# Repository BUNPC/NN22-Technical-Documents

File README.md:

This repository contains the technical documentation used to create all parts of the NN22 whole-head fNIRS system.

A description of the documents contained in this respository and other instructions related to the ninjaNIRS system can be found at openfnirs.org [here](https://openfnirs.org/hardware/ninjanirs2022/).

Please use the [Hardware Forum](https://openfnirs.org/community/hardware-forum/) at openfnirs.org to discuss anything about the ninjaNIRS system.

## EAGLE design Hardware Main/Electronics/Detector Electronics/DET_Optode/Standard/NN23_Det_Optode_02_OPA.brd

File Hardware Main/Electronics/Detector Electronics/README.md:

# Detector Electronics
## Updated 5 August, 2024

All detector related files are located within this folder.

Two versions of the backplane are available, the 6 layer and single layer. The 6 layer folder contains the files for the full height backplane to allow for up to 6 detector interface cards to be connected and the single layer folder contains the files for the system configuration with only one interface card per backboard slot.

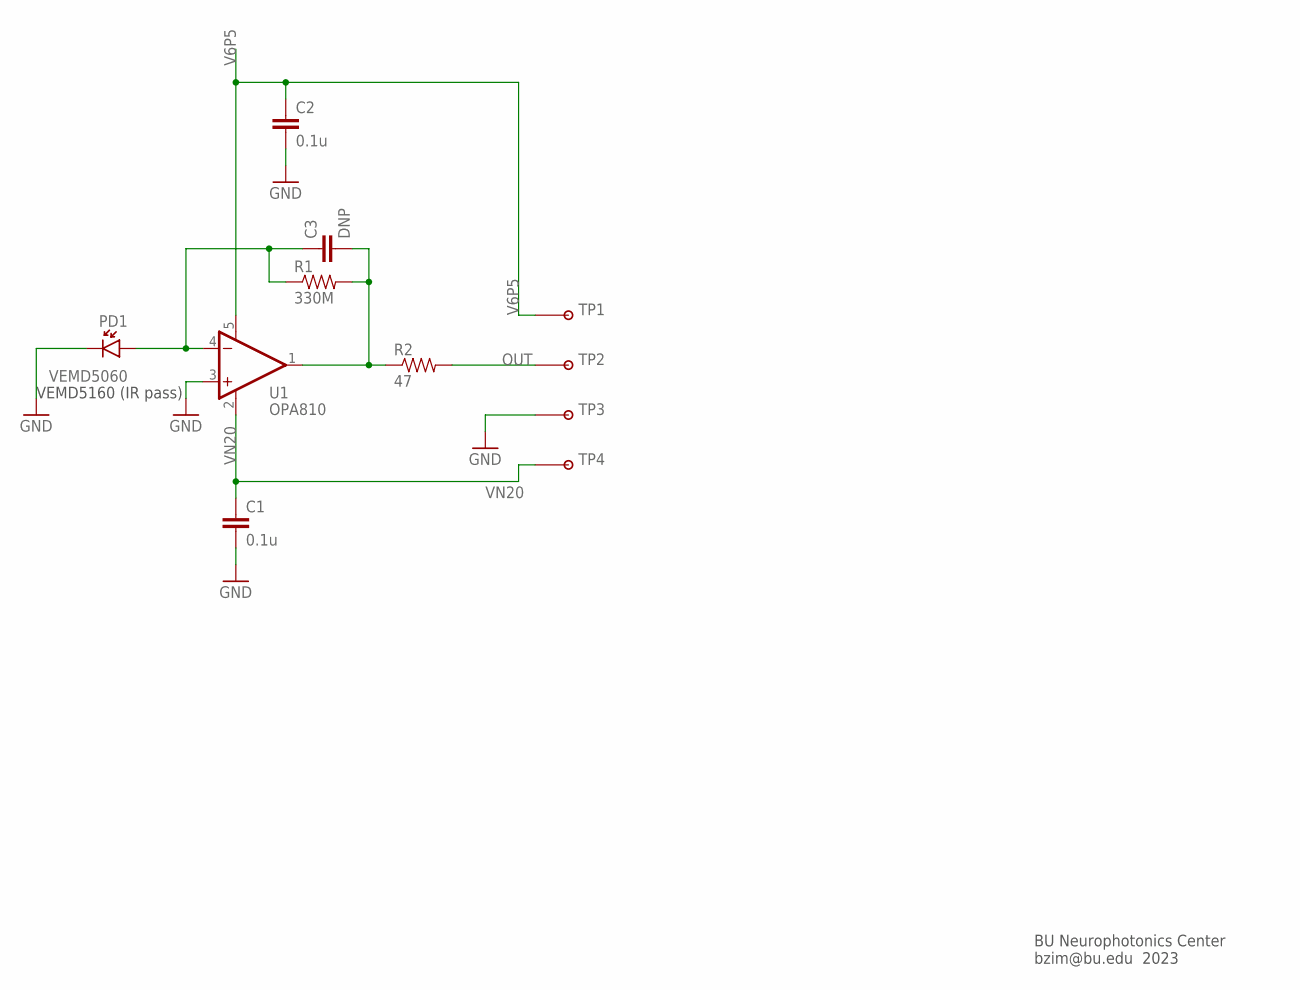
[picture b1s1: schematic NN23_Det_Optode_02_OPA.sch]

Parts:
C1, C2: 0.1u; 0402-CAP
C3: DNP; 0402-CAP
PD1: VEMD5060
R1: 330M; 0402-RES
R2: 47; 0402-RES
TP1, TP2, TP3, TP4: TESTPOINTPADSMALL; TESTPAD_SMALL
U1: OPA810; SOT353

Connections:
GND: C1.2, C2.2, PD1.C1 (C), PD1.C2 (C), TP3.P$1, U1.3 (+IN)
unnamed: C3.2, R1.2, R2.1, U1.1 (OUT)
unnamed: C3.1, PD1.A, R1.1, U1.4 (-IN)
OUT: R2.2, TP2.P$1
V6P5: C2.1, TP1.P$1, U1.5 (V+)
VN20: C1.1, TP4.P$1, U1.2 (V-)

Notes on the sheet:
VEMD5160 (IR pass)
BU Neurophotonics Center bzim@bu.edu 2023

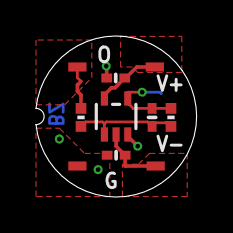
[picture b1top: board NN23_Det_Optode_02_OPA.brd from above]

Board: 2 copper layers, 8.9 x 8.9 mm, 11 parts (1 on the bottom side), 6 nets.

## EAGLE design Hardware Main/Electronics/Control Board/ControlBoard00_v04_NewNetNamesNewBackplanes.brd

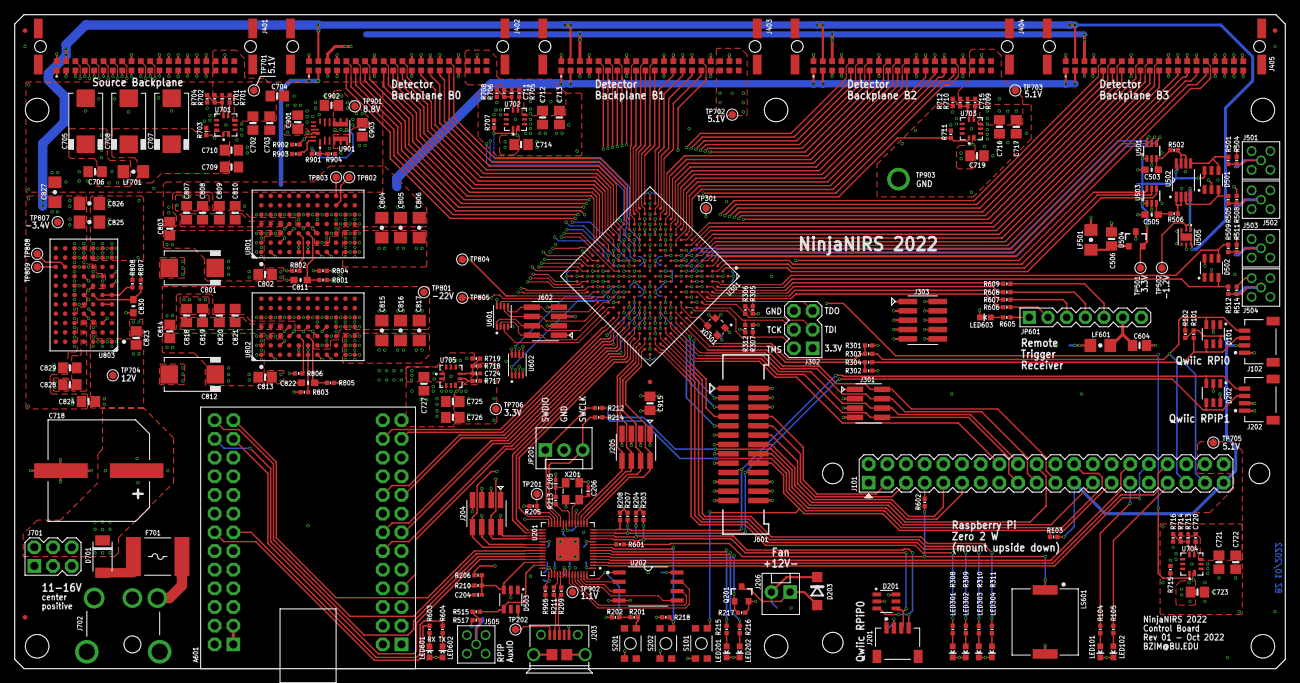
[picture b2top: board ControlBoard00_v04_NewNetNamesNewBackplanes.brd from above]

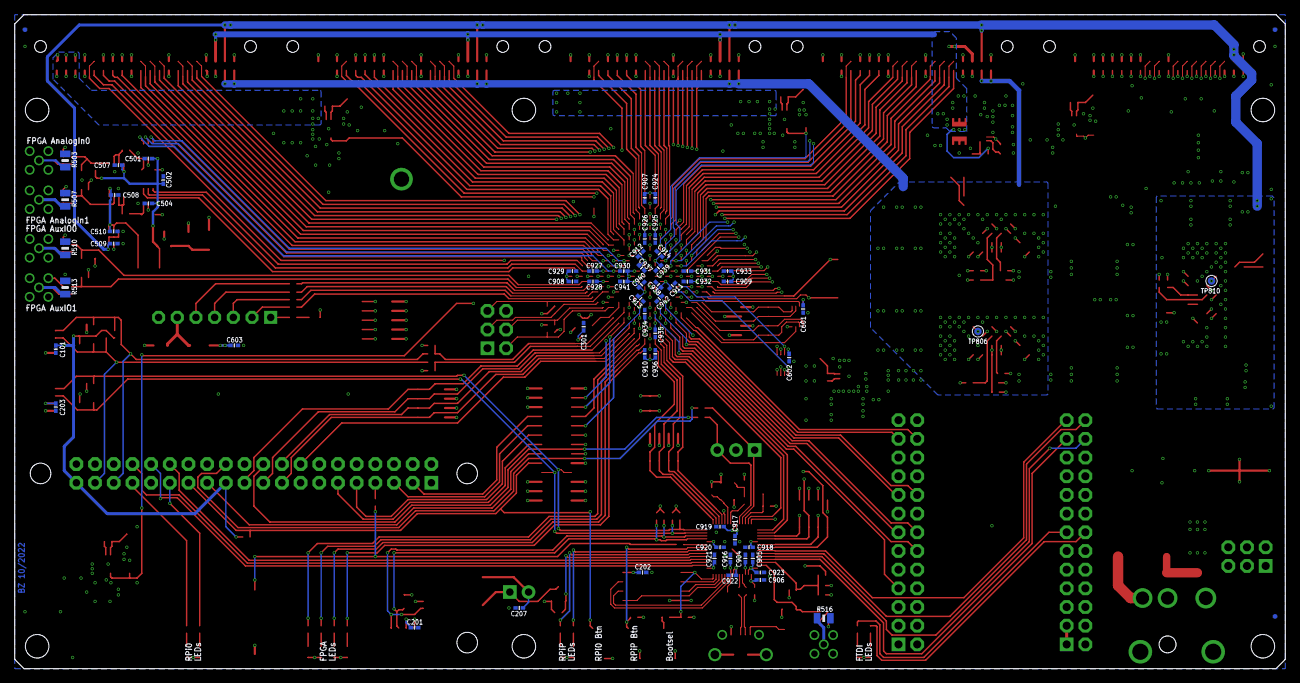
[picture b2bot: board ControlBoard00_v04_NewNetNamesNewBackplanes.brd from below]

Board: 6 copper layers, 172.7 x 88.9 mm, 323 parts (64 on the bottom side), 316 nets.

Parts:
A601: FT2232H-MINIMOD
C101, C201, C202, C203, C204, C207, C301, C501, C504, C507, C508, C601, C602, C603, C916, C917, C918, C919, C920, C921, C922, C923, C924, C925, C926, C927, C928, C929, C930, C931, C932, C933, C934, C935, C936, C937, C938, C939, C940, C941, C942: 0.1u; 0402-CAP
C205, C206: 27p; 0402-CAP
C502, C509, C510, C904, C905, C906, C907, C908, C909, C910, C911, C912, C913, C914: 4.7u; 0402-CAP
C503, C505: 18n; 0603-CAP
C506, C604, C702, C703, C704, C706, C709, C710, C712, C713, C714, C716, C717, C719, C721, C722, C723, C725, C726, C727, C901, C902, C903: 22u; 0805-CAP
C701, C711, C715, C720, C724: 39p; 0402-CAP
C705, C707, C708, C801, C812: 100u/25V; 2917-CAP
C718: 470u/25V; CAP-SMD-POL-12.5
C802, C803, C807, C808, C809, C810, C813, C814, C818, C819, C820, C821, C823, C824, C828, C829: 4.7u; 0805-CAP
C804, C805, C806, C815, C816, C817: 10u; 1206
C811, C822, C830: 1u; 0603-CAP
C825, C826: 100u; 1206
C827: DNP; 1206
C915: DNP; 0805-CAP
D101, D201, D202, D501, D502, D503: D1213A-02SO; SOT23-6
D203: SOD123
D701: SOD128
F701: 2920L600/16MR; 2920-FUSE
FID901, FID902, FID903, FID904, FID905, FID906, FID907: FIDUCIALUFIDUCIAL; MICRO-FIDUCIAL
J101: M20X2_PTH
J102, J201, J202: M04X1_JST_SH_RA; M04X1_JST_SH_SM_RA
J203: USB-MICRO
J204, J205, J301, J602: M04X2_0.050_SMD_NO_CREAM
J206: M02POLAR; MOLEX-1X2
J302, J701: M03X2PTH; 2X3-NS
J303: M05X2_SMD_0.050_NOCREAM; M05X2_0.050_SMD_NO_CREAM
J401, J402, J403, J404, J405: M20X2_HARFLEX_M
J501, J502, J503, J504, J505: SMAMMCX_PTH; MMCX_PTH_STR
J601: M13X2_0.050_SHF
J702: POWERJACK_PJ051AH; PJ051AH
JP201: MOLEX-1X3
JP601: TLW-107-05-G-S; 1X07
LED101, LED201, LED301, LED303, LED601: LTST-C191KRKT; LED-0603
LED102, LED202, LED302, LED304, LED602, LED603: LTST-C191KGKT; LED-0603
LF501, LF601, LF701: FERRITE1206; 1206
LS601: PKMCS0909E4000-R1; XDCR_PKMCS0909E4000-R1
Q201: MOSFET-NCHANNELSMD; SOT23-3
R101, R102, R103, R203, R204, R207, R208, R210, R218, R301, R302, R305, R306, R307, R312, R504, R508, R511, R514, R517: 10k; 0402-RES
R104, R105, R215, R216, R308, R309, R310, R311, R603, R604, R605: 470; 0402-RES
R201, R213, R501, R505, R601, R602, R606, R607, R608, R609, R701, R705, R709, R713, R717: 1k; 0402-RES
R202, R212, R214, R303, R304, R903: DNP; 0402-RES
R205, R217, R703, R707, R711, R715, R804, R902: 100k; 0402-RES
R206, R702, R706, R710, R714, R718: 47k; 0402-RES
R209, R211, R502, R506: 27; 0402-RES
R503, R507, R510, R513, R516: DNP; 0805
R509, R512, R515, R905: 100; 0402-RES
R704, R708, R712, R716: 8.66k; 0402-RES
R719: 15k; 0402-RES
R801, R805: 82; 0402-RES
R802, R806: 180k; 0402-RES
R803: 220k; 0402-RES
R807: 15; 0402-RES
R808, R901: 68k; 0402-RES
R904: 6.8k; 0402-RES
S101, S201, S202: SWITCH-MOMENTARY-2SMD-3; TACTILE_SWITCH_SMD-3
TP201, TP202, TP301, TP501, TP502, TP701, TP702, TP703, TP704, TP705, TP706, TP801, TP802, TP803, TP804, TP805, TP806, TP807, TP808, TP809, TP810, TP901, TP902: TESTPOINT_ROUND; TESTPAD_ROUND
TP903: TESTPOINTTUR; TURRET
U201: RP2040; QFN-56_EP
U202: W25Q_SO; SO08-208MIL
U301: MACHXO2_FTBGA256; LBGA-256
U501, U503: ADS7886; SOT363
U502: LT1801; SOP65P490X110-8N
U504: REF30XX; SOT23-3
U505: ADP7182_WSON; WSON6
U601, U602: APS6404L; USON8L-2X3MM
U701, U702, U703, U704, U705: RPL-30
U801, U802, U803: LTM4651; BGA-77
U901: MPM3620_FULL_CREAM; QFN-20-MPS_FULL_CREAM
X201: CRYSTAL-3.2-2.5
XO301: OSCILLATOR_TXO2520; TXO2520

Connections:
ADS_CSN0: U301.H5, U501.6
ADS_CSN1: U301.C1, U503.6
ADS_SCK0: U301.F5, U501.4
ADS_SCK1: U301.B1, U503.4
ADS_SDO0: U301.G5, U501.5
ADS_SDO1: U301.C2, U503.5
AUXIO0: D502.4, R509.2, U301.B3
AUXIO1: D502.3, R512.2, U301.A3
BOOTSEL: R201.1, S201.4
DETB_END_CYC0: J402.B15, U301.R7
DETB_END_CYC1: J403.B15, U301.P1
DETB_END_CYC2: J404.B15, U301.J1
DETB_END_CYC3: J405.B15, U301.D1
DETB_RUN0: J402.A16, U301.T5
DETB_RUN1: J403.A16, U301.N3
DETB_RUN2: J404.A16, U301.K5
DETB_RUN3: J405.A16, U301.E3
DETB_SELECT00: J402.B11, U301.R9
DETB_SELECT01: J402.B9, U301.R11
DETB_SELECT02: J402.A10, U301.T9
DETB_SELECT03: J402.B7, U301.N9
DETB_SELECT04: J402.B5, U301.N11
DETB_SELECT05: J402.A6, U301.P9
DETB_SELECT06: J403.B11, U301.T2
DETB_SELECT07: J403.B9, U301.T4
DETB_SELECT08: J403.A10, U301.R4
DETB_SELECT09: J403.B7, U301.P5
DETB_SELECT10: J403.B5, U301.N8
DETB_SELECT11: J403.A6, U301.N6
DETB_SELECT12: J404.B11, U301.K2
DETB_SELECT13: J404.B9, U301.M2
DETB_SELECT14: J404.A10, U301.M1
DETB_SELECT15: J404.B7, U301.J4
DETB_SELECT16: J404.B5, U301.L4
DETB_SELECT17: J404.A6, U301.L3
DETB_SELECT18: J405.B11, U301.F2
DETB_SELECT19: J405.B9, U301.H2
DETB_SELECT20: J405.A10, U301.G1
DETB_SELECT21: J405.B7, U301.F4
DETB_SELECT22: J405.B5, U301.H4
DETB_SELECT23: J405.A6, U301.G3
DETB_STATUS_SELECT0: J402.B16, U301.R6
DETB_STATUS_SELECT1: J403.B16, U301.N2
DETB_STATUS_SELECT2: J404.B16, U301.J2
DETB_STATUS_SELECT3: J405.B16, U301.D2
DETB_TRIGGER0: J402.B14, U301.T7
DETB_TRIGGER1: J403.B14, U301.P2
DETB_TRIGGER2: J404.B14, U301.J3
DETB_TRIGGER3: J405.B14, U301.E2
EXP_J303_D0: J303.2, U301.C5
EXP_J303_D1: J303.4, U301.D6
EXP_J303_D2: J303.6, U301.D7
EXP_J303_D3: J303.8, U301.C7
EXP_J601_D0: J601.3, U301.C10
EXP_J601_D1: J601.5, U301.B10
EXP_J601_D2: J601.7, U301.A13
EXP_J601_D3: J601.9, U301.E10
EXP_J601_D4: J601.11, U301.D11
EXP_J601_D5: J601.13, U301.C12
EXP_J601_D6: J601.15, U301.C13
FP_LED0: R308.2, U301.A15
FP_LED1: R309.2, U301.B14
FP_LED2: R310.2, U301.A14
FP_LED3: R311.2, U301.B13
FP_SCL: R301.1, R303.1, U301.A9
FP_SDA: R302.1, R304.1, U301.C9
FT_C0: A601.CN2-18, U301.G16
FT_C1: A601.CN2-17, U301.G15
FT_C2: A601.CN2-20, U301.H13
FT_C5: A601.CN2-24, U301.H16
FT_C6: A601.CN2-23, U301.H15
FT_CTS#: A601.CN3-23, U201.39
FT_D4: A601.CN2-14, U301.G12
FT_D5: A601.CN2-13, U301.F16
FT_D6: A601.CN2-16, U301.G14
FT_D7: A601.CN2-15, U301.G13
FT_RTS#: A601.CN3-24, U201.38
FT_RXD: A601.CN3-25, U201.36
FT_TXD: A601.CN3-26, U201.37
GND: A601.CN2-2, A601.CN2-4, A601.CN2-6, A601.CN3-2, A601.CN3-4, C101.2, C201.2, C202.2, C203.2, C204.2, C205.2, C206.2, C207.2, C301.2, C501.2, C502.2, C503.2, C504.2, C505.2, C506.2, C507.2, C508.1, C509.1, C510.1, C601.2, C602.2, C603.2, C604.2, C702.2, C703.2, C704.2, C705.N, C706.2, C707.N, C708.N, C709.2, C710.2, C712.2, C713.2, C714.2, C716.2, C717.2, C718.N, C719.2, C721.2, C722.2, C723.2, C725.2, C726.2, C727.2, C801.N, C802.2, C804.1, C805.1, C806.1, C807.2, C808.2, C812.N, C813.2, C815.1, C816.1, C817.1, C818.2, C819.2, C823.2, C825.1, C826.1, C827.1, C828.2, C901.2, C902.2, C903.2, C904.2, C905.2, C906.2, C907.2, C908.2, C909.2, C910.2, C911.2, C912.2, C913.2, C914.2, C915.2, C916.2, C917.2, C918.2, C919.2, C920.2, C921.2, C922.2, C923.2, C924.2, C925.2, C926.2, C927.2, C928.2, C929.2, C930.2, C931.2, C932.2, C933.2, C934.2, C935.2, C936.2, C937.2, C938.2, C939.2, C940.2, C941.2, C942.2, D101.2, D201.2, D202.2, D501.2, D502.2, D503.2, J101.1, J101.8, J101.12, J101.15, J101.22, J101.28, J101.31, J101.36, J102.1, J201.1, J202.1, J203.5, J203.SH1, J203.SH2, J203.SH3, J203.SH4, J203.SH5, J203.SH6, J204.1, J204.3, J204.5, J204.7, J205.1, J205.3, J205.5, J205.7, J301.1, J301.3, J301.5, J301.7, J302.6, J303.1, J303.3, J303.5, J303.7, J303.9, J401.A1, J401.A9, J401.A12, J401.A13, J401.A14, J401.A15, J401.A16, J401.A17, J401.A19, J401.B1, J401.B2, J401.B3, J401.B17, J402.A1, J402.A4, J402.A8, J402.A12, J402.A13, J402.A14, J402.A15, J402.A17, J402.A19, J402.B3, J402.B4, J402.B8, J402.B12, J402.B17, J403.A1, J403.A4, J403.A8, J403.A12, J403.A13, J403.A14, J403.A15, J403.A17, J403.A19, J403.B3, J403.B4, J403.B8, J403.B12, J403.B17, J404.A1, J404.A4, J404.A8, J404.A12, J404.A13, J404.A14, J404.A15, J404.A17, J404.A19, J404.B3, J404.B4, J404.B8, J404.B12, J404.B17, J405.A1, J405.A4, J405.A8, J405.A12, J405.A13, J405.A14, J405.A15, J405.A17, J405.A19, J405.B3, J405.B4, J405.B8, J405.B12, J405.B17, J501.G@1, J501.G@2, J501.G@3, J501.G@4, J502.G@1, J502.G@2, J502.G@3, J502.G@4, J503.G@1, J503.G@2, J503.G@3, J503.G@4, J504.G@1, J504.G@2, J504.G@3, J504.G@4, J505.G@1, J505.G@2, J505.G@3, J505.G@4, J601.1, J601.2, J601.4, J601.6, J601.17, J601.21, J601.24, J601.25, J602.1, J602.3, J602.5, J602.7, J701.1, J701.3, J701.5, J702.SHIELD1, J702.SHIELD2, J702.SLEEVE, J702.SWITCH, JP201.2, JP601.7, LED101.C, LED102.C, LED201.C, LED202.C, LED301.C, LED302.C, LED303.C, LED304.C, LED603.C, LS601.2, Q201.2, R210.1, R217.1, R218.1, R312.1, R503.1, R504.1, R507.1, R508.1, R510.1, R511.1, R513.1, R514.1, R516.1, R517.1, R703.1, R704.1, R707.1, R708.1, R711.1, R712.1, R715.1, R716.1, R719.1, R801.2, R804.2, R805.2, R807.2, R902.1, R903.1, R904.1, S101.1, S201.1, TP903.P$1, U201.19, U201.PAD, U202.4, U301.B2, U301.B15, U301.C3, U301.C14, U301.D4, U301.D13, U301.E5, U301.E12, U301.F6, U301.F11, U301.H8, U301.H9, U301.J8, U301.J9, U301.L6, U301.L11, U301.M5, U301.M12, U301.N4, U301.N13, U301.P3, U301.P14, U301.R2, U301.R15, U501.2, U503.2, U504.3, U505.5, U601.4, U602.4, U701.3, U701.4, U701.8, U702.3, U702.4, U702.8, U703.3, U703.4, U703.8, U704.3, U704.4, U704.8, U705.3, U705.4, U705.8, U801.D4, U801.G1, U801.H1, U801.K1, U801.K2, U801.K3, U801.L1, U801.L2, U801.L3, U802.D4, U802.G1, U802.H1, U802.K1, U802.K2, U802.K3, U802.L1, U802.L2, U802.L3, U803.D4, U803.G1, U803.H1, U803.K1, U803.K2, U803.K3, U803.L1, U803.L2, U803.L3, U901.3, U901.12, U901.13, U901.14, X201.2, X201.4, XO301.2
LED: JP601.1, R605.1
unnamed: U803.D3, U803.G3
unnamed: TP802.P$1, U801.J6
unnamed: C701.2, R702.1, R704.2, U701.7
unnamed: R701.1, U701.6
unnamed: U803.E1, U803.E2
unnamed: U801.D3, U801.G3
unnamed: U801.E1, U801.E2, U802.E1, U802.E2
unnamed: A601.CN3-1, A601.CN3-3
unnamed: R802.2, U801.E3
unnamed: F701.1, J702.CENTER
unnamed: TP803.P$1, U801.J7
unnamed: C811.1, R801.1, U801.F3
unnamed: C206.1, U201.20, X201.3
unnamed: C205.1, R213.2, X201.1
unnamed: R213.1, U201.21
unnamed: C822.1, R805.1, U802.F3
unnamed: TP808.P$1, U803.J6
unnamed: TP809.P$1, U803.J7
unnamed: R803.1, U801.F1, U801.F2, U802.F1, U802.F2
unnamed: U802.D3, U802.G3
unnamed: TP806.P$1, U802.H4
unnamed: C830.1, R807.1, U803.F3
unnamed: C807.1, C808.1, C809.1, C810.1, U801.A4, U801.B4, U801.C4
unnamed: C711.2, R706.1, R708.2, U702.7
unnamed: R209.1, U201.47
unnamed: R211.1, U201.46
unnamed: C818.1, C819.1, C820.1, C821.1, U802.A4, U802.B4, U802.C4
unnamed: R806.2, U802.E3
unnamed: R705.1, U702.6
unnamed: C715.2, R710.1, R712.2, U703.7
unnamed: J203.2, R211.2
unnamed: R808.1, U803.F1, U803.F2
unnamed: J203.3, R209.2
unnamed: R709.1, U703.6
unnamed: TP810.P$1, U803.H4
unnamed: C720.2, R714.1, R716.2, U704.7
unnamed: C828.1, C829.1, U803.A4, U803.B4, U803.C4
unnamed: R713.1, U704.6
unnamed: C906.1, R905.2, U201.43
unnamed: C724.2, R718.1, R719.2, U705.7
unnamed: R717.1, U705.6
unnamed: J501.C, R501.1, R503.2, R504.2
unnamed: D501.4, R501.2, U502.5
unnamed: J502.C, R505.1, R507.2, R508.2
unnamed: D501.3, R505.2, U502.3
unnamed: LED601.C, R603.2
unnamed: LED602.C, R604.2
unnamed: J505.C, R515.1, R516.2, R517.2
unnamed: LED301.A, R308.1
unnamed: LED302.A, R309.1
unnamed: LED303.A, R310.1
unnamed: LED304.A, R311.1
unnamed: LS601.1, R601.1, R602.1
unnamed: J503.C, R509.1, R510.2, R511.2
unnamed: J504.C, R512.1, R513.2, R514.2
unnamed: R903.2, U901.18
unnamed: R901.1, R904.2, U901.1
unnamed: C503.1, R502.2, U501.3
unnamed: R502.1, U502.6, U502.7
unnamed: C505.1, R506.2, U503.3
unnamed: R506.1, U502.1, U502.2
unnamed: LED202.A, R216.1
unnamed: LED101.A, R104.1
unnamed: LED102.A, R105.1
unnamed: D701.A, F701.2
unnamed: LED201.A, R215.1
unnamed: D203.A, J206.1, Q201.3
unnamed: C506.1, LF501.2, U504.1
unnamed: JP601.5, R609.2
unnamed: JP601.4, R608.2
unnamed: JP601.3, R607.2
unnamed: JP601.2, R606.2
unnamed: LED603.A, R605.2
OSC_CLK: U301.C8, XO301.3
QSPI_SCLK: U201.52, U202.6
QSPI_SD0: U201.53, U202.5
QSPI_SD1: U201.55, U202.2
QSPI_SD2: U201.54, U202.3
QSPI_SD3: U201.51, U202.7
QSPI_SS_N: R201.2, R202.1, U201.56, U202.1
RAM0_CEN: J602.4, U301.K16, U601.1
RAM0_SCLK: J602.6, U301.K15, U601.6
RAM0_SIO0: J602.8, U301.L16, U601.5
RAM0_SIO1: J602.2, U301.J15, U601.2
RAM0_SIO2: U301.J16, U601.3
RAM0_SIO3: U301.L15, U601.7
RAM1_CEN: U301.J12, U602.1
RAM1_SCLK: U301.K13, U602.6
RAM1_SIO0: U301.K14, U602.5
RAM1_SIO1: U301.J13, U602.2
RAM1_SIO2: U301.J14, U602.3
RAM1_SIO3: U301.K12, U602.7
RPFP_D0: J205.2, U201.15, U301.B16
RPFP_D1: J205.4, U201.16, U301.C15
RPFP_D2: J205.6, U201.17, U301.C16
RPFP_D3: J205.8, U201.18, U301.D15
RPFP_D4: U201.27, U301.D16
RPFP_D5: U201.28, U301.E14
RPFP_D6: U201.29, U301.E15
RPFP_D7: U201.30, U301.E16
RPFP_D8: J204.2, U201.31, U301.T6
RPFP_D9: J204.4, U201.32, U301.R12
RPFP_D10: J204.6, U201.34, U301.P6
RPFP_D11: J204.8, U201.35, U301.P13
RPI0_BUZZ: J101.7, R602.2
RPI0_CE: J101.18, J301.6, U301.B11
RPI0_GPIO5: J101.11, J601.14
RPI0_GPIO6: J101.9, J601.12
RPI0_GPIO7: J101.16, U301.B12
RPI0_GPIO12: J101.10, U301.D9
RPI0_GPIO16: J101.6, U301.E9
RPI0_GPIO18: J101.30, U201.4
RPI0_GPIO19: J101.5, J601.10
RPI0_GPIO20: J101.4, U301.D10
RPI0_GPIO21: J101.2, U301.C11
RPI0_GPIO22: J101.25, J601.16
RPI0_GPIO24: J101.24, R212.1
RPI0_GPIO25: J101.20, R214.1
RPI0_GPIO26: J101.3, J601.8
RPI0_GPIO27: J101.27, J601.18, R103.1, S101.4
RPI0_LED0: J101.29, R104.2
RPI0_LED1: J101.33, R105.2
RPI0_MISO: J101.19, J301.4, U301.A11
RPI0_MOSI: J101.21, J301.2, U301.A10
RPI0_RX0: J101.32, U201.2
RPI0_SCL: D101.3, J101.35, J102.4, R102.1, R303.2
RPI0_SCLK: J101.17, J301.8, U301.A12
RPI0_SDA: D101.4, J101.37, J102.3, R101.1, R304.2
RPI0_TX0: J101.34, U201.3
RPI0_V3P3: C101.1, D101.6, J101.23, J101.39, J102.2, R101.2, R102.2, R103.2
RPIP_AUXIO: D503.4, R515.2, U201.41
RPIP_BTN: R218.2, S202.1, U201.8
RPIP_BUZZ: R601.2, U201.9
RPIP_FAN: Q201.1, R217.2, U201.5
RPIP_LED0: R215.2, U201.7
RPIP_LED1: R216.2, U201.6
RPIP_SCL0: D201.3, J201.4, R204.1, U201.12
RPIP_SCL1: D202.3, J202.4, J601.19, R208.1, U201.14
RPIP_SDA0: D201.4, J201.3, R203.1, U201.11
RPIP_SDA1: D202.4, J202.3, J601.20, R207.1, U201.13
RUN: R205.1, TP201.P$1, U201.26
RXLED#: A601.CN3-14, R603.1
SRC_COL00: J401.A11, U301.M10
SRC_COL01: J401.A10, U301.T12
SRC_COL02: J401.A8, U301.R13
SRC_COL03: J401.A7, U301.R14
SRC_COL04: J401.A6, U301.R16
SRC_COL05: J401.A5, U301.P16
SRC_COL06: J401.B8, U301.T14
SRC_COL07: J401.B7, U301.T15
SRC_COL08: J401.A4, U301.N15
SRC_COL09: J401.A3, U301.M14
SRC_COL10: J401.B10, U301.P12
SRC_COL11: J401.B9, U301.T13
SRC_COL12: J401.B12, U301.M11
SRC_COL13: J401.B11, U301.L10
SRC_PWR0: J401.B6, U301.P15
SRC_PWR1: J401.B5, U301.N14
SRC_PWR2: J401.B4, U301.N16
SRC_ROW0: J401.B16, U301.L9
SRC_ROW1: J401.B15, U301.M9
SRC_ROW2: J401.B14, U301.P11
SRC_SPARE: J401.B13, U301.T11
SWCLK: JP201.3, R214.2, U201.24
SWDIO: JP201.1, R212.2, U201.25
TCK: J302.4, R312.2, U301.A7
TDI: J302.3, R306.1, U301.A6
TDO: J302.5, R305.1, U301.C6
TMS: J302.2, R307.1, U301.B8
TP301_NET: TP301.P$1, U301.J5
TRG0: R609.1, U301.B4
TRG1: R608.1, U301.A4
TRG2: R607.1, U301.B5
TRG3: R606.1, U301.A5
TXLED#: A601.CN3-13, R604.1
UART_CTSN_TO_FTDI: A601.CN2-12, U301.F15
UART_DETB_TO_FPGA00: J402.B10, U301.R10
UART_DETB_TO_FPGA01: J402.A11, U301.T8
UART_DETB_TO_FPGA02: J402.A9, U301.T10
UART_DETB_TO_FPGA03: J402.B6, U301.N10
UART_DETB_TO_FPGA04: J402.A7, U301.P8
UART_DETB_TO_FPGA05: J402.A5, U301.P10
UART_DETB_TO_FPGA06: J403.B10, U301.T3
UART_DETB_TO_FPGA07: J403.A11, U301.R3
UART_DETB_TO_FPGA08: J403.A9, U301.R5
UART_DETB_TO_FPGA09: J403.B6, U301.N7
UART_DETB_TO_FPGA10: J403.A7, U301.P4
UART_DETB_TO_FPGA11: J403.A5, U301.P7
UART_DETB_TO_FPGA12: J404.B10, U301.L2
UART_DETB_TO_FPGA13: J404.A11, U301.L1
UART_DETB_TO_FPGA14: J404.A9, U301.N1
UART_DETB_TO_FPGA15: J404.B6, U301.K4
UART_DETB_TO_FPGA16: J404.A7, U301.K3
UART_DETB_TO_FPGA17: J404.A5, U301.M3
UART_DETB_TO_FPGA18: J405.B10, U301.G2
UART_DETB_TO_FPGA19: J405.A11, U301.F1
UART_DETB_TO_FPGA20: J405.A9, U301.H1
UART_DETB_TO_FPGA21: J405.B6, U301.G4
UART_DETB_TO_FPGA22: J405.A7, U301.F3
UART_DETB_TO_FPGA23: J405.A5, U301.H3
UART_FPGA_TO_DETB0: J402.B13, U301.R8
UART_FPGA_TO_DETB1: J403.B13, U301.R1
UART_FPGA_TO_DETB2: J404.B13, U301.K1
UART_FPGA_TO_DETB3: J405.B13, U301.E1
UART_FPGA_TO_FTDI: A601.CN2-10, U301.F14
UART_FTDI_RXLEDN: A601.CN2-19, U301.H12
UART_FTDI_TO_FPGA: A601.CN2-7, U301.F12
UART_FTDI_TXLEDN: A601.CN2-22, U301.H14
UART_RTSN_TO_FPGA: A601.CN2-9, U301.F13
V1P1: C904.1, C916.1, C917.1, TP902.P$1, U201.23, U201.45, U201.50
V3P3: C201.1, C202.1, C203.1, C301.1, C601.1, C602.1, C603.1, C724.1, C725.1, C726.1, C905.1, C907.1, C908.1, C909.1, C910.1, C911.1, C912.1, C913.1, C914.1, C915.1, C918.1, C919.1, C920.1, C921.1, C922.1, C923.1, C924.1, C925.1, C926.1, C927.1, C928.1, C929.1, C930.1, C931.1, C932.1, C933.1, C934.1, C935.1, C936.1, C937.1, C938.1, C939.1, C940.1, C941.1, C942.1, D201.6, D202.6, D502.6, D503.6, J201.2, J202.2, J302.1, J303.10, J601.22, J601.23, LF601.1, R202.2, R203.2, R204.2, R205.2, R207.2, R208.2, R301.2, R302.2, R305.2, R306.2, R307.2, R717.2, R718.2, R905.1, S202.4, TP706.P$1, U201.1, U201.10, U201.22, U201.33, U201.42, U201.44, U201.48, U201.49, U202.8, U301.A1, U301.A16, U301.D5, U301.D12, U301.E4, U301.E13, U301.G7, U301.G8, U301.G9, U301.G10, U301.H7, U301.H10, U301.J7, U301.J10, U301.K7, U301.K8, U301.K9, U301.K10, U301.M4, U301.M13, U301.N5, U301.N12, U301.T1, U301.T16, U601.8, U602.8, U705.5, XO301.1, XO301.4
V3P3_FTDI: A601.CN2-1, A601.CN2-3, A601.CN2-5, A601.CN2-11, A601.CN2-21, A601.CN3-12, A601.CN3-22, LED601.A, LED602.A
V3P3_R: C604.1, JP601.6, LF601.2
V5P1_B01: C711.1, C712.1, C713.1, J402.A18, J402.A20, J402.B18, J402.B19, J402.B20, J403.A18, J403.A20, J403.B18, J403.B19, J403.B20, R705.2, R706.2, TP702.P$1, U702.5
V5P1_B01_EN: R707.2, U301.M7, U702.1
V5P1_B23: C715.1, C716.1, C717.1, J404.A18, J404.A20, J404.B18, J404.B19, J404.B20, J405.A18, J405.A20, J405.B18, J405.B19, J405.B20, LF501.1, R709.2, R710.2, TP703.P$1, U703.5
V5P1_B23_EN: R711.2, U703.1
V5P1_RPI: C720.1, C721.1, C722.1, J101.38, J101.40, R713.2, R714.2, TP705.P$1, U704.5
V5P1_RPI_EN: R715.2, U301.B7, U704.1
V5P1_SRC: C701.1, C702.1, C703.1, C704.1, J401.A18, J401.A20, J401.B18, J401.B19, J401.B20, R701.2, R702.2, TP701.P$1, U701.5
V5P1_SRC_EN: R703.2, U301.L8, U701.1
V9P0: C902.1, C903.1, J402.A3, J403.A3, J404.A3, J405.A3, R901.2, TP901.P$1, U901.7_8_9
V9P0_EN: R902.2, U301.M8, U901.17
V12: C207.1, C705.P, C706.1, C714.1, C718.P, C719.1, C723.1, C727.1, C801.P, C802.1, C803.1, C812.P, C813.1, C814.1, C823.1, C824.1, C901.1, D203.C, D701.C, J206.2, J601.26, J701.2, J701.4, J701.6, LF701.1, R206.2, TP704.P$1, U702.2, U703.2, U704.2, U705.1, U705.2, U801.A1, U801.A2, U801.A3, U801.B3, U801.C3, U802.A1, U802.A2, U802.A3, U802.B3, U802.C3, U803.A1, U803.A2, U803.A3, U803.B3, U803.C3, U901.16
V12_SRC: C707.P, C708.P, C709.1, C710.1, LF701.2, U701.2
VA_3P3: C501.1, C502.1, C504.1, C507.1, D501.6, TP501.P$1, U501.1, U502.8, U503.1, U504.2
VBUS: J203.1, TP202.P$1
VIN_SENSE: C204.1, D503.3, R206.1, R210.2, U201.40
VN1P2: C508.2, C510.2, TP502.P$1, U502.4, U505.1, U505.2
VN3P4: C509.2, C824.2, C825.2, C826.2, C827.2, C829.2, C830.2, J401.A2, J402.A2, J403.A2, J404.A2, J405.A2, R808.2, TP807.P$1, U505.3, U505.6, U505.PAD, U803.A5, U803.B5, U803.C2, U803.C5, U803.D5, U803.E4, U803.E5, U803.F5, U803.G2, U803.G4, U803.G5, U803.H2, U803.H3, U803.H5, U803.J3, U803.J4, U803.J5, U803.K4, U803.K5, U803.L4, U803.L5
VN3P4_EN: U301.L14, U803.F4
VN22: C803.2, C804.2, C805.2, C806.2, C809.2, C810.2, C811.2, C814.2, C815.2, C816.2, C817.2, C820.2, C821.2, C822.2, J402.B1, J402.B2, J403.B1, J403.B2, J404.B1, J404.B2, J405.B1, J405.B2, R802.1, R803.2, R806.1, TP801.P$1, U801.A5, U801.B5, U801.C2, U801.C5, U801.D5, U801.E4, U801.E5, U801.F5, U801.G2, U801.G4, U801.G5, U801.H2, U801.H3, U801.H5, U801.J3, U801.J4, U801.J5, U801.K4, U801.K5, U801.L4, U801.L5, U802.A5, U802.B5, U802.C2, U802.C5, U802.D5, U802.E4, U802.E5, U802.F5, U802.G2, U802.G4, U802.G5, U802.H2, U802.H3, U802.H5, U802.J3, U802.J4, U802.J5, U802.K4, U802.K5, U802.L4, U802.L5
VN22_CLKA: TP804.P$1, U301.M15, U801.B1
VN22_CLKB: TP805.P$1, U301.M16, U802.B1
VN22_EN: R804.1, U301.L13, U801.F4, U802.F4

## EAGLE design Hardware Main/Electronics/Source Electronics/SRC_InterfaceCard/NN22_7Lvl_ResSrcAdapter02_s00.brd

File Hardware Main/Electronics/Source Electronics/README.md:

# Source Electronics
## Updated 5 August, 2024

All source related files are located within this folder.

Two versions of the backplane are available, the 7 layer and single layer. 
- The 7 layer folder contains the files for the full height backplane to allow for up to 7 source interface cards to be connected.
- The single layer folder contains the files for the system configuration with only one interface card per backboard slot.

Two optode types are available, one standard source optode and one co-located optode.
- Standard source optode has been designed to fit in the spring loaded cap mounts made for the NIRx NIRSport 2 system
- Colocated source optode has been designed to mount on top of the active wet electrodes for the LiveAmp 8/16/32/64 EEG systems. All enclosure documents have also been included.

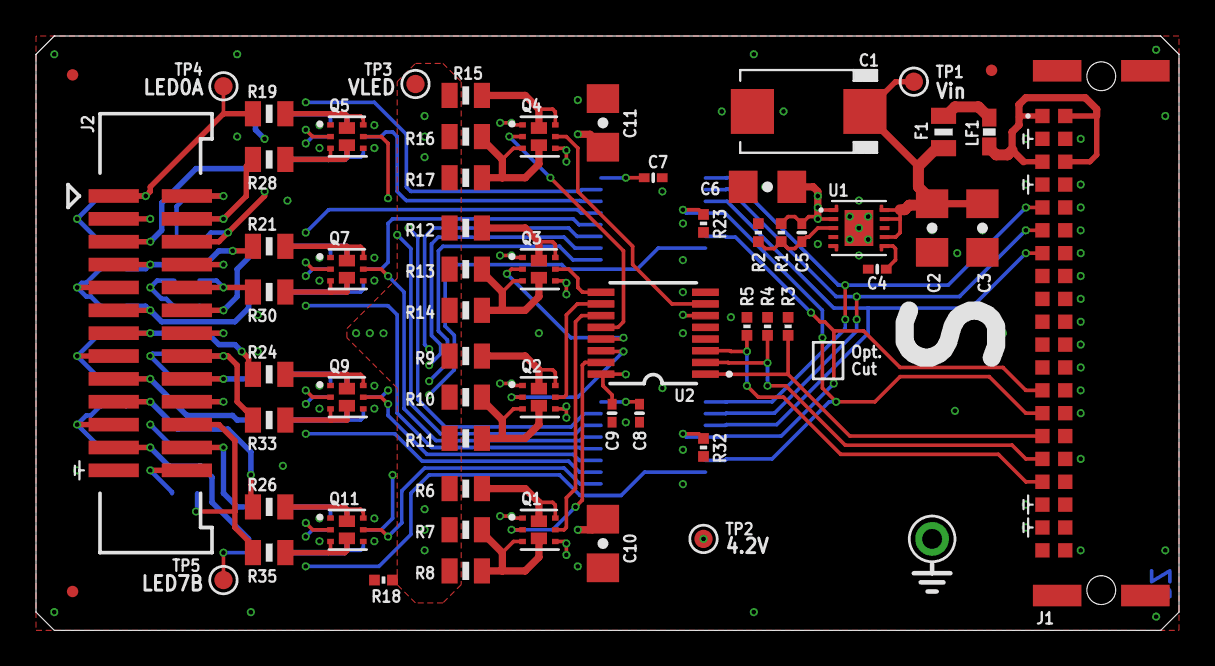
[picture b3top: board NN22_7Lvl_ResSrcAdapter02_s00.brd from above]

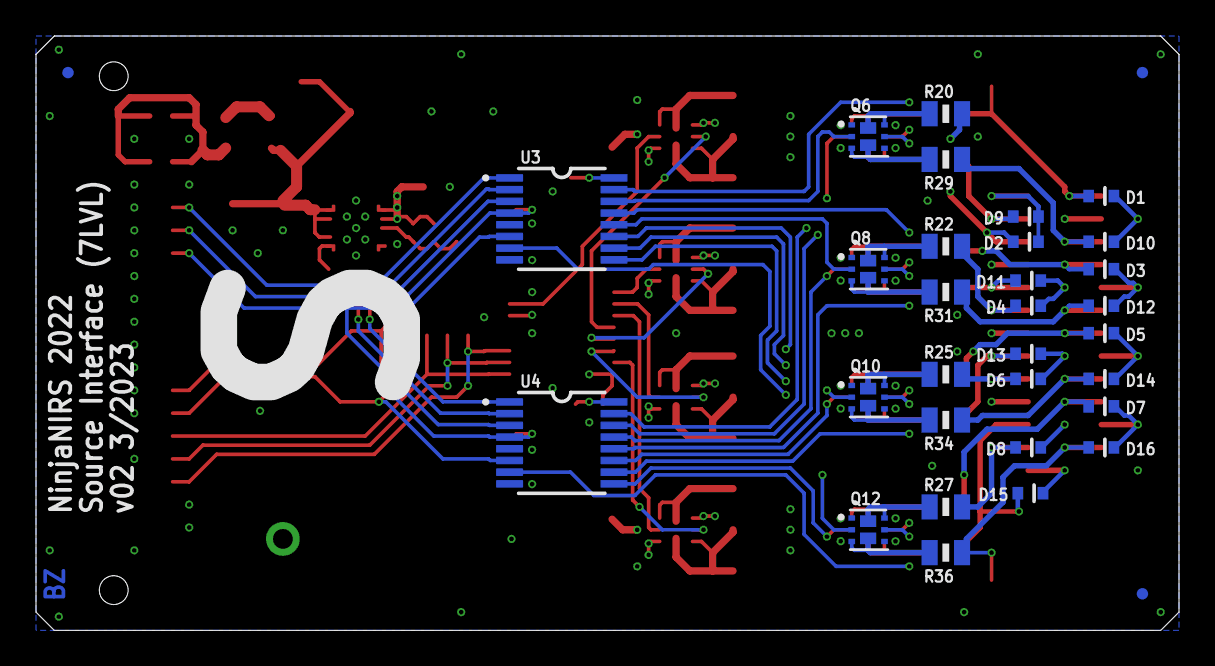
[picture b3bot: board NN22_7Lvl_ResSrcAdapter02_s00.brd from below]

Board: 4 copper layers, 63.5 x 33.0 mm, 95 parts (33 on the bottom side), 80 nets.

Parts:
C1: 100u; 2917-CAP
C2, C3, C6, C10, C11: 22u; 1206
C4, C7, C8, C9: 0.1u; 0402-CAP
C5: 47p; 0402-CAP
D1, D2, D3, D4, D5, D6, D7, D8, D9, D10, D11, D12, D13, D14, D15, D16: SBR1A20T5; SOD523
F1: SMD0805B050TF; 0805
FID1, FID2, FID3, FID4, FID5, FID6: FIDUCIALUFIDUCIAL; MICRO-FIDUCIAL
J1: M20X2_HARFLEX_M
J2: M13X2_0.050_SHF
LF1: FERRITE0603; 0603-FER
Q1, Q2, Q3, Q4: MOSFET-DUAL-P-UDFN8; UDFN8
Q5, Q6, Q7, Q8, Q9, Q10, Q11, Q12: MOSFET-DUAL-N-UDFN8; UDFN8
R1: 2.7k; 0402-RES
R2: 365; 0402-RES
R3, R4, R5, R18, R23, R32: 100k; 0402-RES
R6, R11: DNP; 0805
R7, R8, R15: 270; 0805
R9: 1.2k; 0805
R10, R13, R14: 39; 0805
R12: 560; 0805
R16, R17: 15; 0805
R19, R20, R21, R22, R24, R25, R26, R27: 5.1; 0805
R28, R29, R30, R31, R33, R34, R35, R36: 6.2; 0805
TP1, TP2, TP3, TP4, TP5: TESTPOINT_ROUND; TESTPAD_ROUND
TP6: TESTPOINT1X01; 1X01
U1: ISL80103; DFN10_ISL
U2: 74HC138_TSSOP; TSSOP16
U3, U4: 74HC238_TSSOP; TSSOP16

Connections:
COLA: J1.B13, R32.2, U3.6, U4.4
COLB: J1.B14, R23.2, U3.4, U4.6
GND: C1.N, C2.2, C3.2, C4.2, C6.2, C7.2, C8.2, C9.2, C10.2, C11.2, J1.A2, J1.A4, J1.A5, J1.A6, J1.A7, J1.A8, J1.A9, J1.A10, J1.A11, J1.A12, J1.A13, J1.A14, J1.A16, J1.A20, J1.B2, J1.B4, J1.B18, J1.B19, J2.25, Q5.1, Q5.4, Q6.1, Q6.4, Q7.1, Q7.4, Q8.1, Q8.4, Q9.1, Q9.4, Q10.1, Q10.4, Q11.1, Q11.4, Q12.1, Q12.4, R2.1, R3.1, R4.1, R5.1, R18.1, R23.1, R32.1, TP6.1, U1.4, U1.5, U1.PAD, U2.4, U2.5, U2.8, U3.5, U3.8, U4.5, U4.8
LED_0A: D1.A, J2.1, R19.2, TP4.P$1
LED_0B: D9.A, J2.4, R28.2
LED_1A: D2.A, J2.6, R20.2
LED_1B: D10.A, J2.5, R29.2
LED_2A: D3.A, J2.7, R21.2
LED_2B: D11.A, J2.10, R30.2
LED_3A: D4.A, J2.12, R22.2
LED_3B: D12.A, J2.11, R31.2
LED_4A: D5.A, J2.13, R24.2
LED_4B: D13.A, J2.16, R33.2
LED_5A: D6.A, J2.18, R25.2
LED_5B: D14.A, J2.17, R34.2
LED_6A: D7.A, J2.19, R26.2
LED_6B: D15.A, J2.22, R35.2
LED_7A: D8.A, J2.24, R27.2
LED_7B: D16.A, J2.23, R36.2, TP5.P$1
unnamed: Q7.2, U3.13
unnamed: Q7.6, Q7.P1, R21.1
unnamed: C4.1, U1.6
unnamed: Q5.2, U3.15
unnamed: Q5.6, Q5.P1, R19.1
unnamed: Q1.2, U2.15
unnamed: Q2.2, U2.14
unnamed: Q5.5, U4.15
unnamed: Q5.3, Q5.P2, R28.1
unnamed: Q8.2, U3.12
unnamed: Q3.2, U2.13
unnamed: Q4.2, U2.12
unnamed: Q7.5, U4.13
unnamed: Q7.3, Q7.P2, R30.1
unnamed: Q6.2, U3.14
unnamed: Q6.6, Q6.P1, R20.1
unnamed: Q1.5, U2.11
unnamed: Q2.5, U2.10
unnamed: Q6.5, U4.14
unnamed: Q6.3, Q6.P2, R29.1
unnamed: Q3.5, U2.9
unnamed: Q4.5, U2.7
unnamed: Q1.6, Q1.P1, R6.2
unnamed: Q1.3, Q1.P2, R7.2, R8.2
unnamed: Q2.3, Q2.P2, R10.2, R11.2
unnamed: Q8.6, Q8.P1, R22.1
unnamed: Q2.6, Q2.P1, R9.2
unnamed: Q3.6, Q3.P1, R12.2
unnamed: Q8.5, U4.12
unnamed: Q8.3, Q8.P2, R31.1
unnamed: Q3.3, Q3.P2, R13.2, R14.2
unnamed: Q4.6, Q4.P1, R15.2
unnamed: Q9.2, U3.11
unnamed: Q9.6, Q9.P1, R24.1
unnamed: Q4.3, Q4.P2, R16.2, R17.2
unnamed: Q9.5, U4.11
unnamed: Q9.3, Q9.P2, R33.1
unnamed: Q10.2, U3.10
unnamed: Q10.6, Q10.P1, R25.1
unnamed: Q10.5, U4.10
unnamed: Q10.3, Q10.P2, R34.1
unnamed: Q11.2, U3.9
unnamed: Q11.6, Q11.P1, R26.1
unnamed: Q11.5, U4.9
unnamed: Q11.3, Q11.P2, R35.1
unnamed: Q12.2, U3.7
unnamed: Q12.6, Q12.P1, R27.1
unnamed: Q12.5, U4.7
unnamed: Q12.3, Q12.P2, R36.1
unnamed: F1.1, LF1.2
unnamed: C1.P, C2.1, C3.1, F1.2, TP1.P$1, U1.7, U1.9, U1.10
unnamed: C5.2, R1.1, R2.2, U1.3
PWR0: J1.B15, R3.2, U2.1
PWR1: J1.B16, R4.2, U2.2
PWR2: J1.B17, R5.2, U2.3
ROW0: J1.B5, U3.1, U4.1
ROW1: J1.B6, U3.2, U4.2
ROW2: J1.B7, U3.3, U4.3
V4P2: C5.1, C6.1, C7.1, C8.1, C9.1, C10.1, C11.1, Q1.1, Q1.4, Q2.1, Q2.4, Q3.1, Q3.4, Q4.1, Q4.4, R1.2, TP2.P$1, U1.1, U1.2, U2.6, U2.16, U3.16, U4.16
V5P0_IN: J1.A1, J1.A3, J1.B1, J1.B3, LF1.1
VLED: D1.C, D2.C, D3.C, D4.C, D5.C, D6.C, D7.C, D8.C, D9.C, D10.C, D11.C, D12.C, D13.C, D14.C, D15.C, D16.C, J2.2, J2.3, J2.8, J2.9, J2.14, J2.15, J2.20, J2.21, J2.26, R6.1, R7.1, R8.1, R9.1, R10.1, R11.1, R12.1, R13.1, R14.1, R15.1, R16.1, R17.1, R18.2, TP3.P$1

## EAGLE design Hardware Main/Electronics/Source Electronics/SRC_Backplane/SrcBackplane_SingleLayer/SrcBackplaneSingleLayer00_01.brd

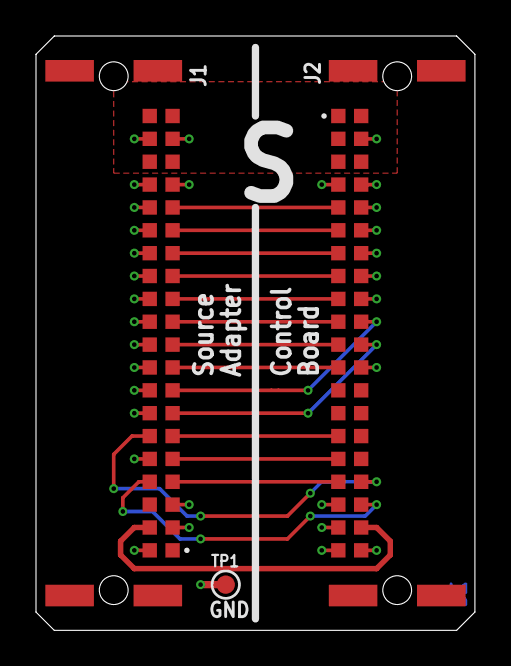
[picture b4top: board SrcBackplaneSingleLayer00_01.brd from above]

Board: 2 copper layers, 24.4 x 33.0 mm, 3 parts (0 on the bottom side), 18 nets.

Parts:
J1, J2: M20X2_HARFLEX_M
TP1: TESTPOINT_ROUND; TESTPAD_ROUND

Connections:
COL00: J1.B8, J2.A10
COL01: J1.B7, J2.A11
COL08: J1.A6, J2.A17
COL09: J1.A4, J2.A18
COL10: J1.B10, J2.B11
COL11: J1.B9, J2.B12
COL12: J1.B12, J2.B9
COL13: J1.B11, J2.B10
GND: J1.A1, J1.A5, J1.A7, J1.A8, J1.A9, J1.A10, J1.A11, J1.A12, J1.A13, J1.A14, J1.A15, J1.A16, J1.A17, J1.A19, J1.B2, J1.B3, J1.B17, J1.B19, J2.A2, J2.A4, J2.A5, J2.A6, J2.A7, J2.A8, J2.A9, J2.A12, J2.A20, J2.B4, J2.B18, J2.B19, J2.B20, TP1.P$1
PWR0: J1.B6, J2.B15
PWR1: J1.B5, J2.B16
PWR2: J1.B4, J2.B17
ROW0: J1.B16, J2.B5
ROW1: J1.B15, J2.B6
ROW2: J1.B14, J2.B7
SPARE: J1.B13, J2.B8
V5P1: J1.A18, J1.A20, J1.B18, J1.B20, J2.A1, J2.A3, J2.B1, J2.B2, J2.B3
VN3P4: J1.A2, J2.A19

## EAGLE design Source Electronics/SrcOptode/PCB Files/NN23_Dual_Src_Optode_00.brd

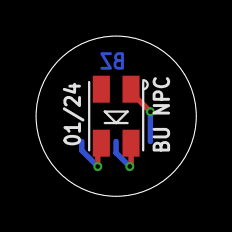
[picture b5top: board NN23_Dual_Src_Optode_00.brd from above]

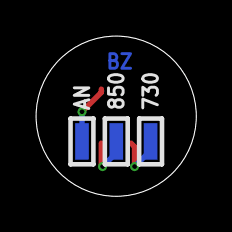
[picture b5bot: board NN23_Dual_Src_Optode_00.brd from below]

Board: 2 copper layers, 8.9 x 8.9 mm, 4 parts (3 on the bottom side), 3 nets.

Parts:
LED1: SMT730D_850D
TP1, TP2, TP3: TESTPOINT_PADMEDIUM; TESTPAD_MEDIUM

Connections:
730: LED1.C7, TP1.P$1
850: LED1.C8, TP2.P$1
AN: LED1.A, TP3.P$1

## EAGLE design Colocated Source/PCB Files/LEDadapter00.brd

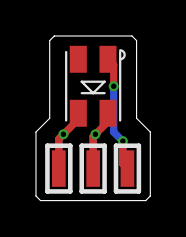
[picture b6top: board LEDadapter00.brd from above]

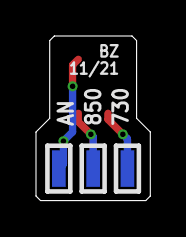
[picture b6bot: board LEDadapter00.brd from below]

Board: 2 copper layers, 6.3 x 9.1 mm, 7 parts (3 on the bottom side), 3 nets.

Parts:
LED1: SMT730D_850D
TP1, TP2, TP3, TP4, TP5, TP6: TESTPOINT_PADMEDIUM; TESTPAD_MEDIUM

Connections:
730: LED1.C7, TP1.P$1, TP6.P$1
850: LED1.C8, TP2.P$1, TP5.P$1
AN: LED1.A, TP3.P$1, TP4.P$1

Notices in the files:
parts and their libraries:
SparkFun-Connectors: Licensing: Creative Commons ShareAlike 4.0 International - https://creativecommons.org/licenses/by-sa/4.0
